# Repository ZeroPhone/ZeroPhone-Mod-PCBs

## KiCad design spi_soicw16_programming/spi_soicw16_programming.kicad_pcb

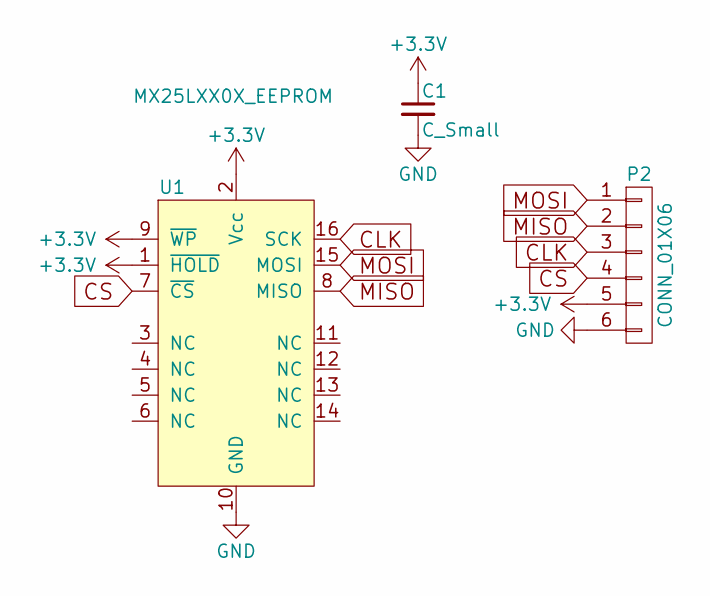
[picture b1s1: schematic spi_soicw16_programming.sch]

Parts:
C1: C_Small; C_0805_HandSoldering
P2: CONN_01X06; Pin_Header_Straight_1x06_Pitch2.54mm
U1: MX25LXX0X_EEPROM; SOIC-16W_7.5x10.3mm_Pitch1.27mm

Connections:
+3V3: C1.1, P2.5, U1.1 (~HOLD), U1.2 (Vcc), U1.9 (~WP)
CLK: P2.3, U1.16 (SCK)
CS: P2.4, U1.7 (~CS)
GND: C1.2, P2.6, U1.10 (GND)
MISO: P2.2, U1.8 (MISO)
MOSI: P2.1, U1.15 (MOSI)

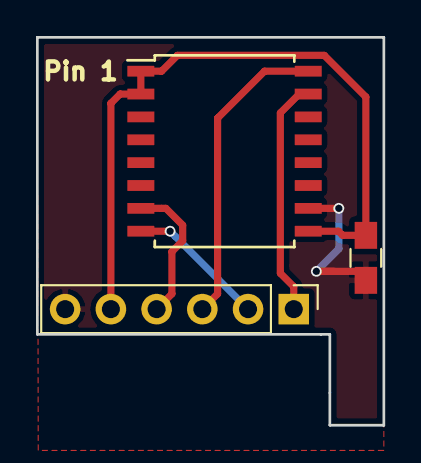
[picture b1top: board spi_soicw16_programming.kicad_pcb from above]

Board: 2 copper layers, 19.2 x 21.5 mm, 3 parts (0 on the bottom side), 6 nets.

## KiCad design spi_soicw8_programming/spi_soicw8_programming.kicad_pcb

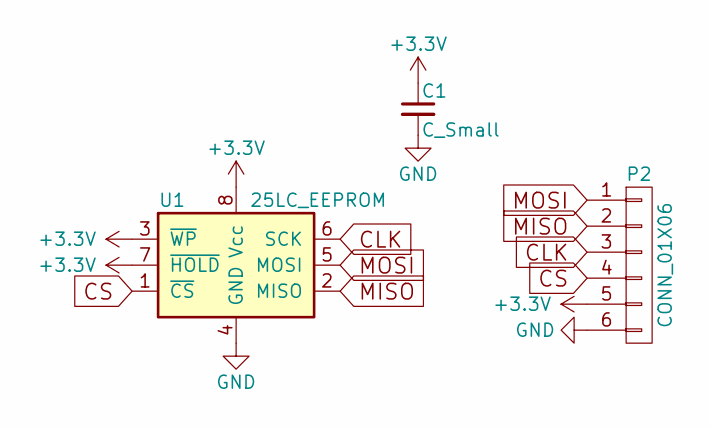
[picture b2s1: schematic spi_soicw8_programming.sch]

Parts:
C1: C_Small; C_0805_HandSoldering
P2: CONN_01X06; Pin_Header_Straight_1x06_Pitch2.54mm
U1: 25LC_EEPROM; SOIJ-8_5.3x5.3mm_Pitch1.27mm

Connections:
+3V3: C1.1, P2.5, U1.3 (~WP), U1.7 (~HOLD), U1.8 (Vcc)
CLK: P2.3, U1.6 (SCK)
CS: P2.4, U1.1 (~CS)
GND: C1.2, P2.6, U1.4 (GND)
MISO: P2.2, U1.2 (MISO)
MOSI: P2.1, U1.5 (MOSI)

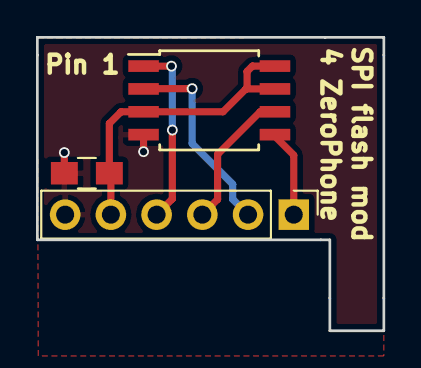
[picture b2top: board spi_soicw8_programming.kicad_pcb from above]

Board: 2 copper layers, 19.2 x 16.3 mm, 3 parts (0 on the bottom side), 6 nets.

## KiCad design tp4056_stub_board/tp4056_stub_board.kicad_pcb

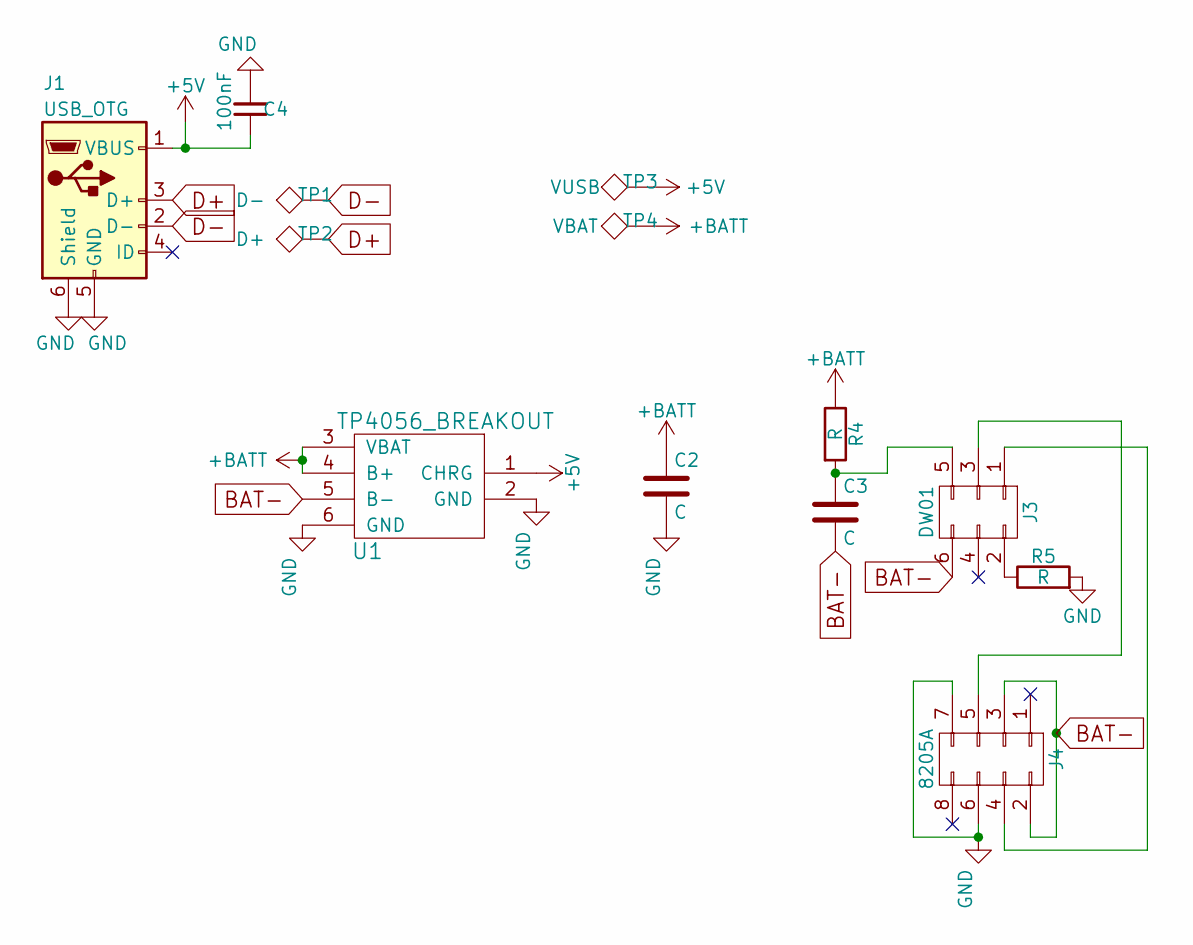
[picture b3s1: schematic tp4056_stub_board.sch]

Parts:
C2: C; C_0603
C3: C; C_0805
C4: 100nF; C_0603
J1: USB_OTG; MICROUSB_SIMPLE
J3: DW01; SOT-23-6
J4: 8205A; TSSOP-8_4.4x3mm_Pitch0.65mm
R4, R5: R; R_0603
TP1: D-; Measurement_Point_Round-SMD-Pad_Small
TP2: D+; Measurement_Point_Round-SMD-Pad_Small
TP3: VUSB; Measurement_Point_Square-SMD-Pad_Big
TP4: VBAT; Measurement_Point_Square-SMD-Pad_Big
U1: TP4056_BREAKOUT

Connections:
+5V: C4.1, J1.1 (VBUS), TP3.1, U1.1 (CHRG)
+BATT: C2.1, R4.1, TP4.1, U1.3 (VBAT), U1.4 (B+)
BAT-: C3.2, J3.6, J4.2, J4.3, U1.5 (B-)
D+: J1.3 (D+), TP2.1
D-: J1.2 (D-), TP1.1
GND: C2.2, C4.2, J1.5 (GND), J1.6 (Shield), J4.6, J4.7, R5.2, U1.2 (GND), U1.6 (GND)
unnamed: C3.1, J3.5, R4.2
unnamed: J3.1, J4.4
unnamed: J3.2, R5.1
unnamed: J3.3, J4.5

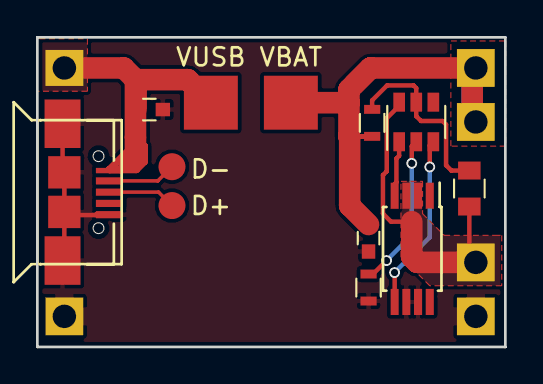
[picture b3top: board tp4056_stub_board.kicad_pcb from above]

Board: 2 copper layers, 26.0 x 17.2 mm, 13 parts (0 on the bottom side), 10 nets.

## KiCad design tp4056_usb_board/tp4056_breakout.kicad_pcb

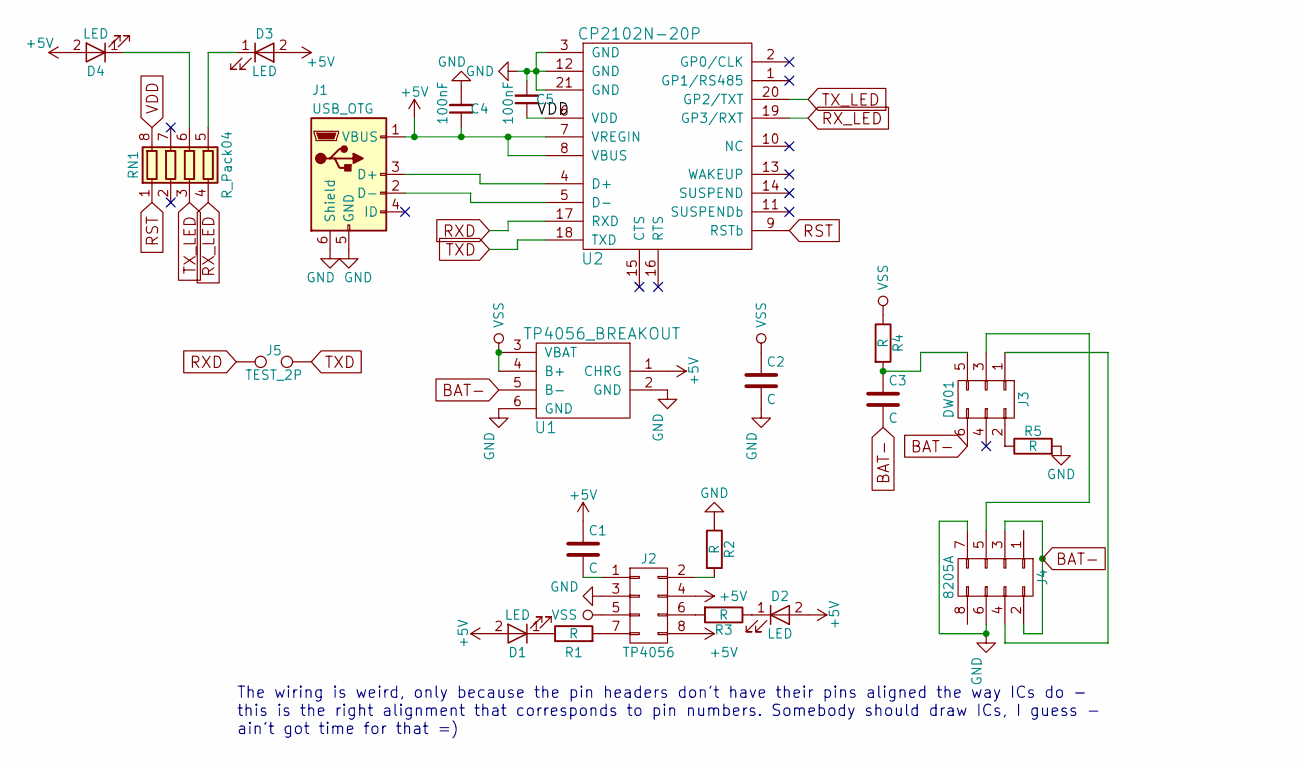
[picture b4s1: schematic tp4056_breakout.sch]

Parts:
C1, C2: C; C_0603
C3: C; C_0805
C4, C5: 100nF; C_0603
D1, D2, D3, D4: LED; R_0603_HandSoldering
J1: USB_OTG; MICROUSB_SIMPLE
J2: TP4056; SOIC-8_3.9x4.9mm_Pitch1.27mm
J3: DW01; SOT-23-6
J4: 8205A; TSSOP-8_4.4x3mm_Pitch0.65mm
J5: TEST_2P; Pin_Header_Straight_1x02_Pitch2.00mm
R1, R2, R3, R4, R5: R; R_0603
RN1: R_Pack04; R_Array_Concave_4x0402
U1: TP4056_BREAKOUT
U2: CP2102N-20P; QFN-20-1EP_3x3mm_Pitch0.5

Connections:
+5V: C1.1, C4.1, D1.2 (A), D2.2 (A), D3.2 (A), D4.2 (A), J1.1 (VBUS), J2.4, J2.8, U1.1 (CHRG), U2.7 (VREGIN), U2.8 (VBUS)
BAT-: C3.2, J3.6, J4.2, J4.3, U1.5 (B-)
GND: C2.2, C4.2, C5.2, J1.5 (GND), J1.6 (Shield), J2.3, J4.6, J4.7, R2.1, R5.2, U1.2 (GND), U1.6 (GND), U2.3 (GND), U2.12 (GND), U2.21 (GND)
unnamed: C1.2, J2.1
unnamed: C3.1, J3.5, R4.2
unnamed: D1.1 (K), R1.1
unnamed: D2.1 (K), R3.1
unnamed: D3.1 (K), RN1.5 (R4.2)
unnamed: D4.1 (K), RN1.6 (R3.2)
unnamed: J1.2 (D-), U2.5 (D-)
unnamed: J1.3 (D+), U2.4 (D+)
unnamed: J2.2, R2.2
unnamed: J2.6, R3.2
unnamed: J2.7, R1.2
unnamed: J3.1, J4.4
unnamed: J3.2, R5.1
unnamed: J3.3, J4.5
RST: RN1.1 (R1.1), U2.9 (RSTb)
RXD: J5.1, U2.17 (RXD)
RX_LED: RN1.4 (R4.1), U2.19 (GP3/RXT)
TXD: J5.2, U2.18 (TXD)
TX_LED: RN1.3 (R3.1), U2.20 (GP2/TXT)
VDD: C5.1, RN1.8 (R1.2), U2.6 (VDD)
VSS: C2.1, J2.5, R4.1, U1.3 (VBAT), U1.4 (B+)

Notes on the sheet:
The wiring is weird, only because the pin headers don't have their pins aligned the way ICs do - this is the right alignment that corresponds to pin numbers. Somebody should draw ICs, I guess - ain't got time for that =)

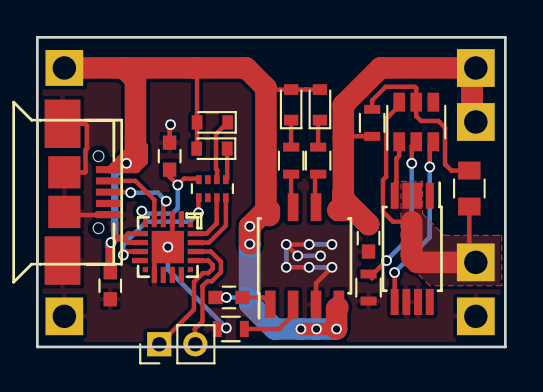
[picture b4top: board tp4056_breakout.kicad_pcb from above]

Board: 2 copper layers, 26.0 x 17.2 mm, 22 parts (0 on the bottom side), 24 nets.

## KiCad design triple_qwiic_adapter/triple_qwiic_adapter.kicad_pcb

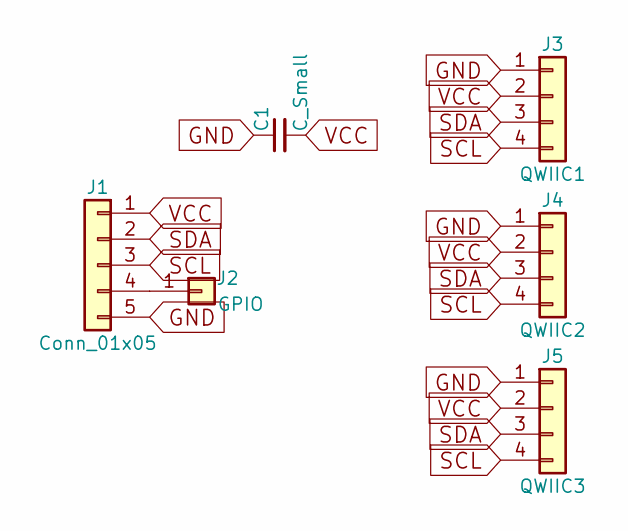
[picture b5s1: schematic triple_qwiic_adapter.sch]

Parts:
C1: C_Small; C_0603
J1: Conn_01x05; Pin_Header_Straight_1x05_Pitch2.54mm
J2: GPIO; Pin_Header_Straight_1x01_Pitch2.00mm
J3: QWIIC1; JST_SH_SM04B-SRSS-TB_04x1.00mm_Angled
J4: QWIIC2; JST_SH_SM04B-SRSS-TB_04x1.00mm_Angled
J5: QWIIC3; JST_SH_SM04B-SRSS-TB_04x1.00mm_Angled

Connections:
GND: C1.1, J1.5, J3.1, J4.1, J5.1
unnamed: J1.4, J2.1
SCL: J1.3, J3.4, J4.4, J5.4
SDA: J1.2, J3.3, J4.3, J5.3
VCC: C1.2, J1.1, J3.2, J4.2, J5.2

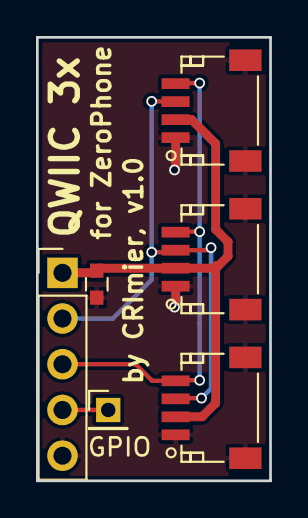
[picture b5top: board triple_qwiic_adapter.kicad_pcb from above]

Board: 2 copper layers, 13.0 x 24.6 mm, 6 parts (0 on the bottom side), 5 nets.

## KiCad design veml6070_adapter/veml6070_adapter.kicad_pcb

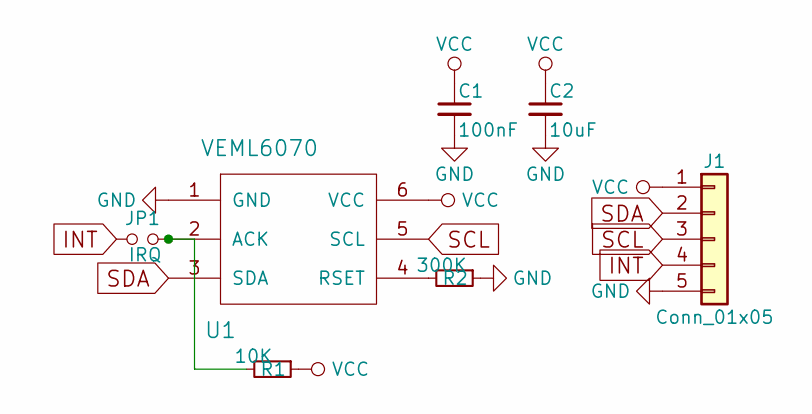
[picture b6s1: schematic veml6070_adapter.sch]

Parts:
C1: 100nF; C_0805
C2: 10uF; C_0805
J1: Conn_01x05; Pin_Header_Straight_1x05_Pitch2.54mm
JP1: IRQ; GS2
R1: 10K; R_0603
R2: 300K; R_0603
U1: VEML6070; OLPGA-6-2.35x1.8

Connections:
GND: C1.2, C2.2, J1.5, R2.1, U1.1 (GND)
INT: J1.4, JP1.1
unnamed: JP1.2, R1.2, U1.2 (ACK)
unnamed: R2.2, U1.4 (RSET)
SCL: J1.3, U1.5 (SCL)
SDA: J1.2, U1.3 (SDA)
VCC: C1.1, C2.1, J1.1, R1.1, U1.6 (VCC)

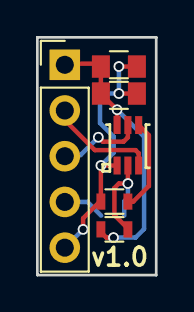
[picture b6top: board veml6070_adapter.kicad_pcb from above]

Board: 2 copper layers, 6.6 x 13.2 mm, 7 parts (1 on the bottom side), 7 nets.
